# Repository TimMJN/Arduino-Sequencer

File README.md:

# Arduino Sequencer
This projects contains schematics and firmware for a step sequencer compatible with Eurorack and Kosmo modular synthesizers, based on an Arduino Nano. This is a DIY project, suitable for beginners, although a general knowledge of electronics, basic tools and skills are required to build this sequencer. The schematics presented here feature:

- 8 steps, 2 voices
- Clock/reset/flip direction inputs
- Random sequence switch
- Buffered gate outputs per step
- Buffered CV outputs per voice
- Scale/offset controls
- Glide controls

Any builder is encouraged to experiment and make changed to the project to suit their needs. By the use of 74HC595 Serial-In-Parallel-Out shift registers to drive the step signals, this sequencer can be easily extended to 16, 32, 64 or even more steps. Similarly, additional voice can be easily added. I'll keep updating the project and documentation as I go.

A [short demonstration](https://youtu.be/yhleVjD8cbQ) is available in YouTube. View the [schematic](schematic+BOM/arduino_sequencer.pdf) and [bill of materials](https://htmlpreview.github.io/?https://github.com/TimMJN/Arduino-Sequencer/blob/main/schematic%2BBOM/arduino_sequencer_BOM.html) on this repository.

# Frequently Asked Questions
## The build
#### Do you have PCBs / panels available?
A PCB design for Kosmo format is available, along with a panel drill guide. I might have some PCBs available, please get in touch. However, it is also possible to build this design on perfboard/stripboard. I want to encourage any builder to come up with their own panel layout, make whatever feels natural to them. If you document your work, I'll be happy to add it here for future reference.

#### How to I add more steps?
Simply copy the main sequencer section as many times as you like. The connections between the 74HC595s are noted in the schematic. The latch and clock pins simply connect together, the serial out of each register connects to the serial in of the next. In the code, change the value of `N_STEPS` and voila!

#### How to I add more voices?
Copy the row of potentiometers/diodes in the main sequencer section as many times as you like. Don't forget to also copy the asociated output circuitry!

#### Can I leave out the gate buffers?
Yes you can. It would be best practice the keep them, but they could be replaced by just a protection diode (e.g. 1N1418).

#### Can I leave out the offset/scale/glide?
I would advice against using no buffering at all, but you could replace this section with just a unity gain buffer. It's also possible to leave out only the glide components, in which case you can also do without the non-inverting buffer behind it.

#### Can I leave out the input protection?
This I would strongly advice against. It's very easy to fry the Arduino by plugging in the wrong signal. You could simplify to a voltage clamp using two Schottky diodes, but I don't see the point in not doing it properly. If you do go with that option, don't forget to change to input logic to track rising instead of falling edges, as the current set-up inverts the inputs.

#### Can I leave out the randomise switch?
Yes, just simply don't include it.

## The code
#### Why don't you use `shiftOut`?
The serial output code I wrote here does the exact same thing as `shiftOut`. I only adapted it to output any number of steps, as the standard 8 bits by `shiftOut`.

#### What's this `interrupt` business?
This allows that Arduino to stop whatever it's doing when it receives a pulse on the clock input and update to the next step. That means that the polling of the other input pins will never slow down the progressing to the next step. Neat!

## The patch
#### Why can't I change the sequence length?
You can, simply patch the gate of the last step to the reset input.

#### Why can't I set a back-and-forth pattern?
You can, simply patch one or two of the gates to the flip input.

# License
All designs in this repository are released under GPL-3.0 licence. Feel free to use and adapt them to your heart's desire. I only ask to refrain from mass-production and commercialisation of PCBs/modules, as I rely on PCB sales for funding new module designs. If you use (parts of) my designs in your own modules, please credit me on your schematics and PCBs to help users find the original creator. I call upon your good conscience to make fair use of my work shared here.

# Support
If you like the resources I have made available here, and wish to support the development of new modules, feel free to buy me a few components through a small donation. I mainly design modules for fun, but you probably already know it can be a costly endeavour. All small contributions help me, thank you very much!

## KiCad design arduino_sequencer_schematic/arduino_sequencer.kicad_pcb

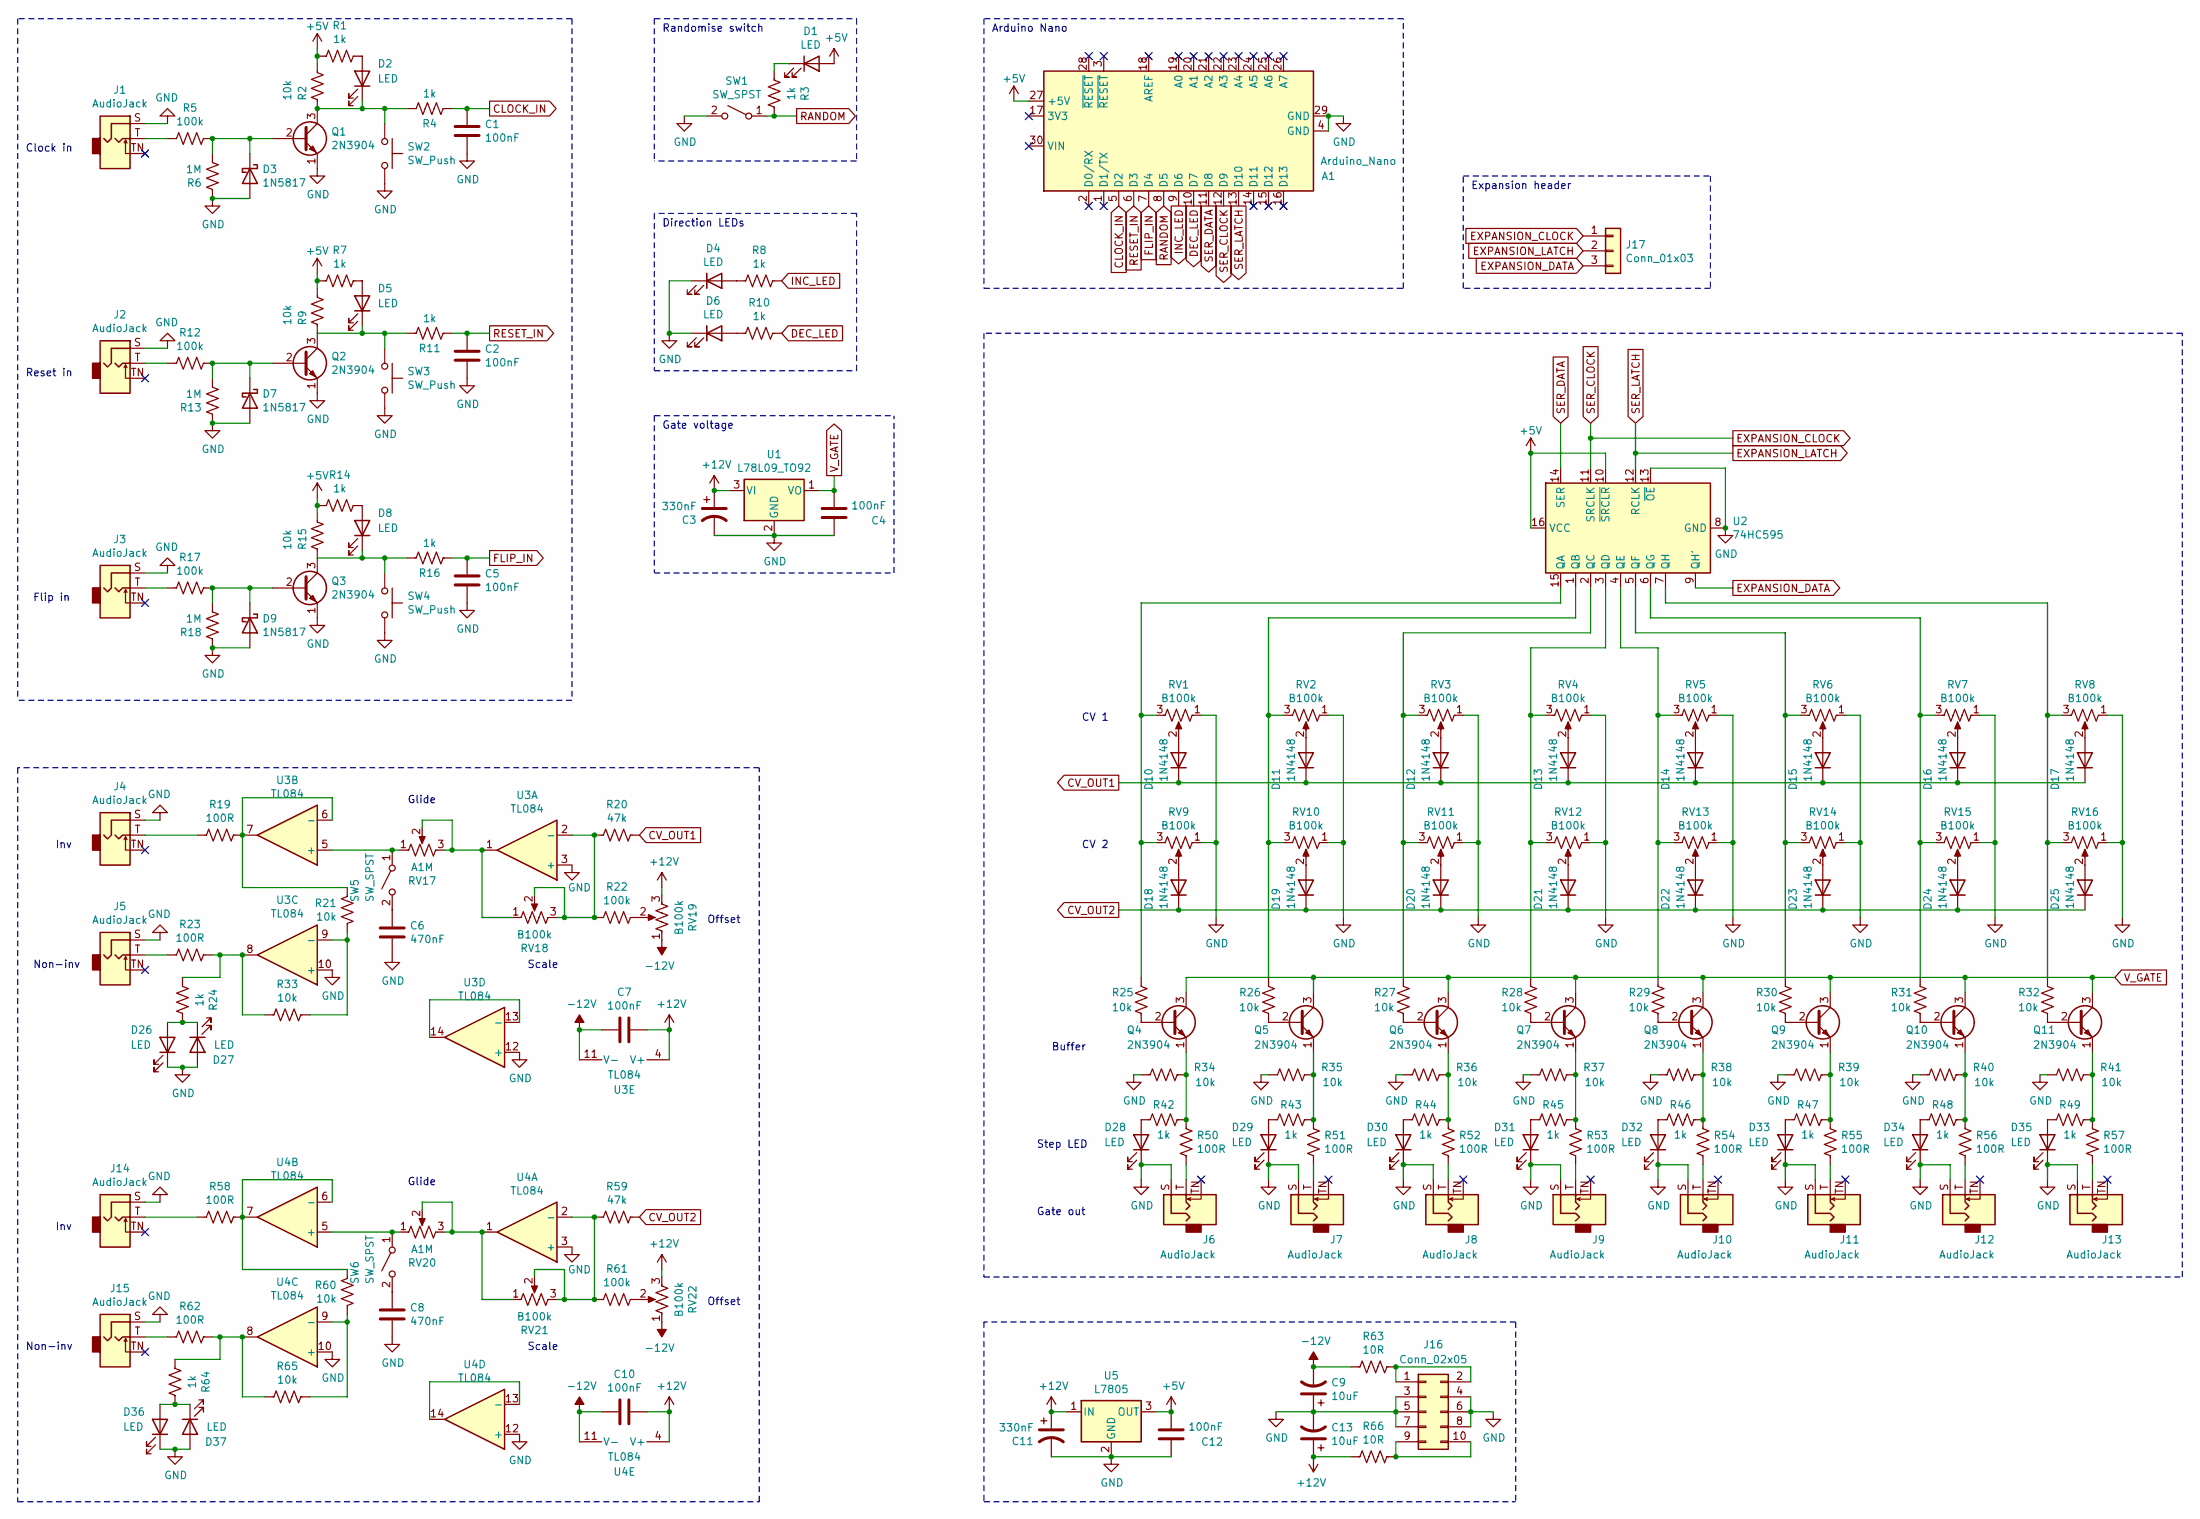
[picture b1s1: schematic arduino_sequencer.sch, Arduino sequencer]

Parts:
A1: Arduino_Nano; Arduino_Nano_2x_header
C1, C2, C4, C5, C7, C10, C12: 100nF; C_Disc_D6.0mm_W2.5mm_P5.00mm
C3, C11: 330nF; CP_Radial_D10.0mm_P3.80mm
C6, C8: 470nF; C_Disc_D14.5mm_W5.0mm_P7.50mm
C9, C13: 10uF; CP_Radial_D10.0mm_P3.80mm
D1, D2, D4, D5, D6, D8, D26, D27, D28, D29, D30, D31, D32, D33, D34, D35, D36, D37: LED; LED_D5.0mm
D3, D7, D9: 1N5817; D_DO-41_SOD81_P10.16mm_Horizontal
D10, D11, D12, D13, D14, D15, D16, D17, D18, D19, D20, D21, D22, D23, D24, D25: 1N4148; D_DO-35_SOD27_P7.62mm_Horizontal
J1, J2, J3, J4, J5, J6, J7, J8, J9, J10, J11, J12, J13, J14, J15: AudioJack; Jack_JST_conn_1x02_P2.50mm
J16: Conn_02x05; IDC-Header_2x05_P2.54mm_Vertical
J17: Conn_01x03; JST_EH_B3B-EH-A_1x03_P2.50mm_Vertical
Q1, Q2, Q3, Q4, Q5, Q6, Q7, Q8, Q9, Q10, Q11: 2N3904; TO-92_Inline
R1, R3, R4, R7, R8, R10, R11, R14, R16, R24, R42, R43, R44, R45, R46, R47, R48, R49, R64: 1k; R_Axial_DIN0207_L6.3mm_D2.5mm_P10.16mm_Horizontal_Value_Sil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
R2, R9, R15, R21, R25, R26, R27, R28, R29, R30, R31, R32, R33, R34, R35, R36, R37, R38, R39, R40, R41, R60, R65: 10k; R_Axial_DIN0207_L6.3mm_D2.5mm_P10.16mm_Horizontal_Value_Sil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
R5, R12, R17, R22, R61: 100k; R_Axial_DIN0207_L6.3mm_D2.5mm_P10.16mm_Horizontal_Value_Sil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
R6, R13, R18: 1M; R_Axial_DIN0207_L6.3mm_D2.5mm_P10.16mm_Horizontal_Value_Sil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
R19, R23, R50, R51, R52, R53, R54, R55, R56, R57, R58, R62: 100R; R_Axial_DIN0207_L6.3mm_D2.5mm_P10.16mm_Horizontal_Value_Sil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
R20, R59: 47k; R_Axial_DIN0207_L6.3mm_D2.5mm_P10.16mm_Horizontal_Value_Sil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
R63, R66: 10R; R_Axial_DIN0207_L6.3mm_D2.5mm_P10.16mm_Horizontal_Value_Sil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
RV1, RV2, RV3, RV4, RV5, RV6, RV7, RV8, RV9, RV10, RV11, RV12, RV13, RV14, RV15, RV16, RV18, RV19, RV21, RV22: B100k; Potentiometer_Alpha_RD901F-40-00D_Single_Vertical
RV17, RV20: A1M; Potentiometer_Alpha_RD901F-40-00D_Single_Vertical
SW1, SW5, SW6: SW_SPST; Switch_SP
SW2, SW3, SW4: SW_Push; Mom_push_button_PBS-110
U1: L78L09_TO92; TO-92_Inline
U2: 74HC595; DIP-16_W7.62mm
U3, U4: TL084; DIP-14_W7.62mm
U5: L7805; TO-220-3_Vertical

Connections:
+5V: A1.27 (+5V), C12.2, D1.2 (A), R1.2, R2.1, R7.2, R9.1, R14.2, R15.1, U2.10 (~SRCLR), U2.16 (VCC), U5.3 (OUT)
+12V: C3.1, C7.1, C10.1, C11.1, C13.1, R66.2, RV19.3, RV22.3, U1.3 (VI), U3.4 (V+), U4.4 (V+), U5.1 (IN)
-12V: C7.2, C9.2, C10.2, R63.2, RV19.1, RV22.1, U3.11 (V-), U4.11 (V-)
CLOCK_IN: A1.5 (D2), C1.1, R4.2
CV_OUT1: D10.1 (K), D11.1 (K), D12.1 (K), D13.1 (K), D14.1 (K), D15.1 (K), D16.1 (K), D17.1 (K), R20.1
CV_OUT2: D18.1 (K), D19.1 (K), D20.1 (K), D21.1 (K), D22.1 (K), D23.1 (K), D24.1 (K), D25.1 (K), R59.1
DEC_LED: A1.10 (D7), R10.1
EXPANSION_CLOCK: A1.12 (D9), J17.1, U2.11 (SRCLK)
EXPANSION_DATA: J17.3, U2.9 (QH')
EXPANSION_LATCH: A1.13 (D10), J17.2, U2.12 (RCLK)
FLIP_IN: A1.7 (D4), C5.1, R16.2
GND: A1.4 (GND), A1.29 (GND), C1.2, C2.2, C3.2, C4.1, C5.2, C6.2, C8.2, C9.1, C11.2, C12.1, C13.2, D3.2 (A), D4.1 (K), D6.1 (K), D7.2 (A), D9.2 (A), D26.1 (K), D27.2 (A), D28.1 (K), D29.1 (K), D30.1 (K), D31.1 (K), D32.1 (K), D33.1 (K), D34.1 (K), D35.1 (K), D36.1 (K), D37.2 (A), J1.S, J2.S, J3.S, J4.S, J5.S, J6.S, J7.S, J8.S, J9.S, J10.S, J11.S, J12.S, J13.S, J14.S, J15.S, J16.3, J16.4, J16.5, J16.6, J16.7, J16.8, Q1.1 (E), Q2.1 (E), Q3.1 (E), R6.1, R13.1, R18.1, R34.1, R35.1, R36.1, R37.1, R38.1, R39.1, R40.1, R41.1, RV1.1, RV2.1, RV3.1, RV4.1, RV5.1, RV6.1, RV7.1, RV8.1, RV9.1, RV10.1, RV11.1, RV12.1, RV13.1, RV14.1, RV15.1, RV16.1, SW1.2 (B), SW2.2, SW3.2, SW4.2, U1.2 (GND), U2.8 (GND), U2.13 (~OE), U3.3 (+), U3.10 (+), U3.12 (+), U4.3 (+), U4.10 (+), U4.12 (+), U5.2 (GND)
INC_LED: A1.9 (D6), R8.1
unnamed: C6.1, SW5.2 (B)
unnamed: C8.1, SW6.2 (B)
unnamed: D1.1 (K), R3.2
unnamed: D2.1 (K), Q1.3 (C), R2.2, R4.1, SW2.1
unnamed: D2.2 (A), R1.1
unnamed: D3.1 (K), Q1.2 (B), R5.1, R6.2
unnamed: D4.2 (A), R8.2
unnamed: D5.1 (K), Q2.3 (C), R9.2, R11.1, SW3.1
unnamed: D5.2 (A), R7.1
unnamed: D6.2 (A), R10.2
unnamed: D7.1 (K), Q2.2 (B), R12.1, R13.2
unnamed: D8.1 (K), Q3.3 (C), R15.2, R16.1, SW4.1
unnamed: D8.2 (A), R14.1
unnamed: D9.1 (K), Q3.2 (B), R17.1, R18.2
unnamed: D10.2 (A), RV1.2
unnamed: D11.2 (A), RV2.2
unnamed: D12.2 (A), RV3.2
unnamed: D13.2 (A), RV4.2
unnamed: D14.2 (A), RV5.2
unnamed: D15.2 (A), RV6.2
unnamed: D16.2 (A), RV7.2
unnamed: D17.2 (A), RV8.2
unnamed: D18.2 (A), RV9.2
unnamed: D19.2 (A), RV10.2
unnamed: D20.2 (A), RV11.2
unnamed: D21.2 (A), RV12.2
unnamed: D22.2 (A), RV13.2
unnamed: D23.2 (A), RV14.2
unnamed: D24.2 (A), RV15.2
unnamed: D25.2 (A), RV16.2
unnamed: D26.2 (A), D27.1 (K), R24.1
unnamed: D28.2 (A), R42.1
unnamed: D29.2 (A), R43.1
unnamed: D30.2 (A), R44.1
unnamed: D31.2 (A), R45.1
unnamed: D32.2 (A), R46.1
unnamed: D33.2 (A), R47.1
unnamed: D34.2 (A), R48.1
unnamed: D35.2 (A), R49.1
unnamed: D36.2 (A), D37.1 (K), R64.1
unnamed: J1.T, R5.2
unnamed: J2.T, R12.2
unnamed: J3.T, R17.2
unnamed: J4.T, R19.2
unnamed: J5.T, R23.2
unnamed: J6.T, R50.2
unnamed: J7.T, R51.2
unnamed: J8.T, R52.2
unnamed: J9.T, R53.2
unnamed: J10.T, R54.2
unnamed: J11.T, R55.2
unnamed: J12.T, R56.2
unnamed: J13.T, R57.2
unnamed: J14.T, R58.2
unnamed: J15.T, R62.2
unnamed: J16.1, J16.2, R63.1
unnamed: J16.9, J16.10, R66.1
unnamed: Q4.1 (E), R34.2, R42.2, R50.1
unnamed: Q4.2 (B), R25.2
unnamed: Q5.1 (E), R35.2, R43.2, R51.1
unnamed: Q5.2 (B), R26.2
unnamed: Q6.1 (E), R36.2, R44.2, R52.1
unnamed: Q6.2 (B), R27.2
unnamed: Q7.1 (E), R37.2, R45.2, R53.1
unnamed: Q7.2 (B), R28.2
unnamed: Q8.1 (E), R38.2, R46.2, R54.1
unnamed: Q8.2 (B), R29.2
unnamed: Q9.1 (E), R39.2, R47.2, R55.1
unnamed: Q9.2 (B), R30.2
unnamed: Q10.1 (E), R40.2, R48.2, R56.1
unnamed: Q10.2 (B), R31.2
unnamed: Q11.1 (E), R41.2, R49.2, R57.1
unnamed: Q11.2 (B), R32.2
unnamed: R19.1, R21.2, U3.6 (-), U3.7
unnamed: R20.2, R22.2, RV18.2, RV18.3, U3.2 (-)
unnamed: R21.1, R33.1, U3.9 (-)
unnamed: R22.1, RV19.2
unnamed: R23.1, R24.2, R33.2, U3.8
unnamed: R25.1, RV1.3, RV9.3, U2.15 (QA)
unnamed: R26.1, RV2.3, RV10.3, U2.1 (QB)
unnamed: R27.1, RV3.3, RV11.3, U2.2 (QC)
unnamed: R28.1, RV4.3, RV12.3, U2.3 (QD)
unnamed: R29.1, RV5.3, RV13.3, U2.4 (QE)
unnamed: R30.1, RV6.3, RV14.3, U2.5 (QF)
unnamed: R31.1, RV7.3, RV15.3, U2.6 (QG)
unnamed: R32.1, RV8.3, RV16.3, U2.7 (QH)
unnamed: R58.1, R60.2, U4.6 (-), U4.7
unnamed: R59.2, R61.2, RV21.2, RV21.3, U4.2 (-)
unnamed: R60.1, R65.1, U4.9 (-)
unnamed: R61.1, RV22.2
unnamed: R62.1, R64.2, R65.2, U4.8
unnamed: RV17.1, SW5.1 (A), U3.5 (+)
unnamed: RV17.2, RV17.3, RV18.1, U3.1
unnamed: RV20.1, SW6.1 (A), U4.5 (+)
unnamed: RV20.2, RV20.3, RV21.1, U4.1
unnamed: U3.13 (-), U3.14
unnamed: U4.13 (-), U4.14
RANDOM: A1.8 (D5), R3.1, SW1.1 (A)
RESET_IN: A1.6 (D3), C2.1, R11.2
SER_DATA: A1.11 (D8), U2.14 (SER)
V_GATE: C4.2, Q4.3 (C), Q5.3 (C), Q6.3 (C), Q7.3 (C), Q8.3 (C), Q9.3 (C), Q10.3 (C), Q11.3 (C), U1.1 (VO)

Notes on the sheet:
Offset
Scale
Glide
Inv
Non-inv
Gate out
Direction LEDs
Randomise switch
Clock in
Reset in
Flip in
Arduino Nano
Step LED
Buffer
CV 1
CV 2
Gate voltage
Expansion header

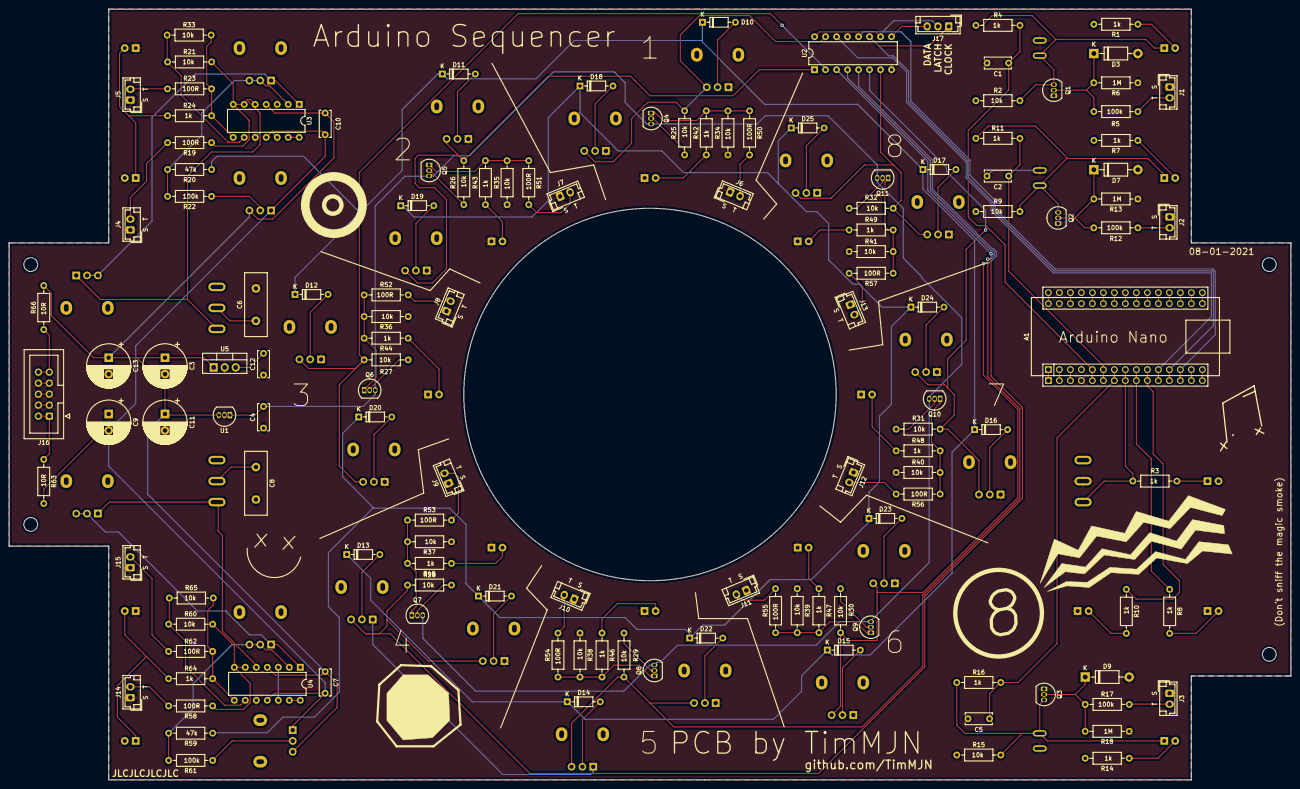
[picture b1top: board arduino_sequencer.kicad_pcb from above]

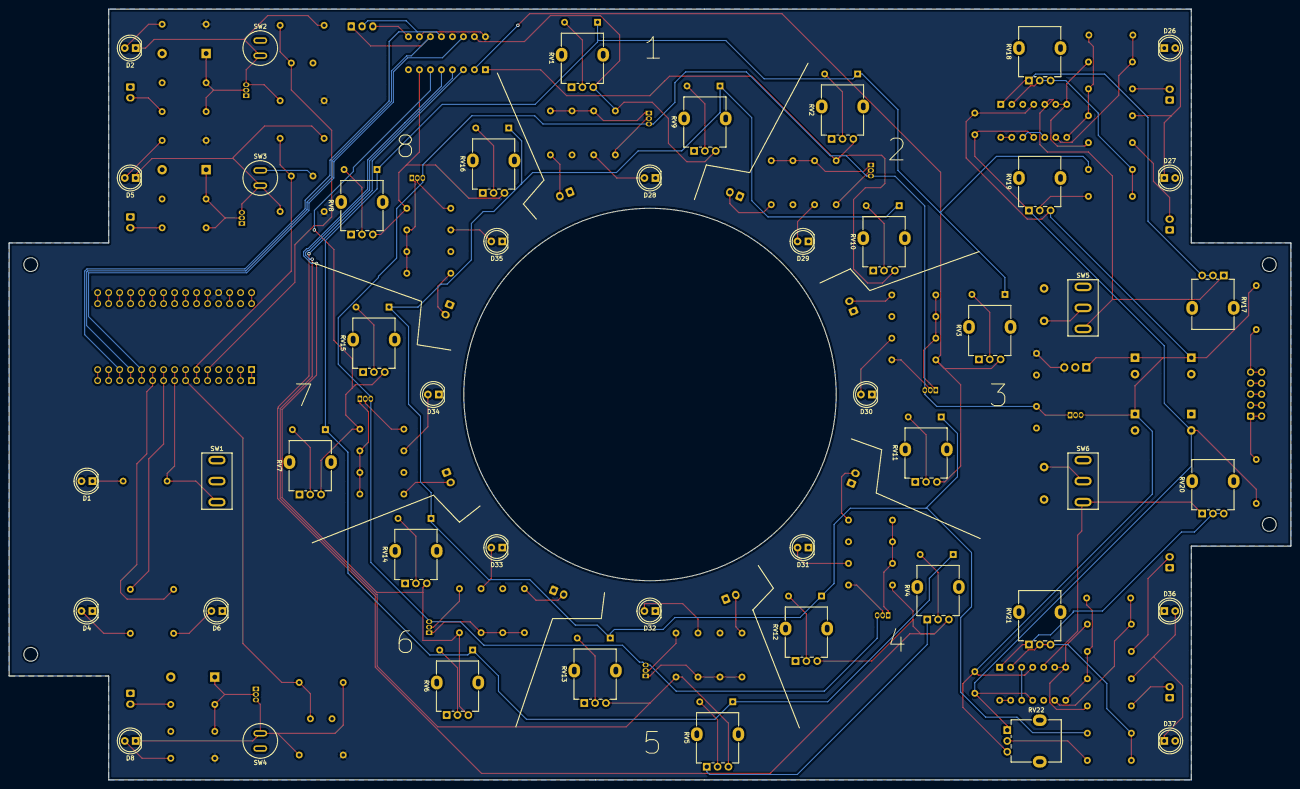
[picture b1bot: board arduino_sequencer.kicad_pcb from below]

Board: 2 copper layers, 296.0 x 178.0 mm, 178 parts (46 on the bottom side), 114 nets.

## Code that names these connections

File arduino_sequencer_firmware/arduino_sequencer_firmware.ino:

////////////////////////////////////////////////////////////////////////////////////////////////////

/* 
 * Arduino Sequencer
 * synthesizer module firmware
 * 
 * by TimMJN
 * 
 * v1.0 
 * 16-01-2021
 * 
 * For schematics and other information, see
 * https://github.com/TimMJN/Arduino-Sequencer
 */

////////////////////////////////////////////////////////////////////////////////////////////////////

// pin definitions
#define CLOCK_PIN     2
#define RESET_PIN     3
#define FLIP_PIN      4
#define RAND_PIN      5
#define INC_LED_PIN   6
#define DEC_LED_PIN   7
#define SER_DATA_PIN  8
#define SER_CLOCK_PIN 9
#define SER_LATCH_PIN 10

#define N_STEPS 8 // number of steps

byte cur_step  = 0; // current step
byte next_step = 0; // next step
bool dir_inc   = true;  // direction (increasing = true, decreasing = false)
bool reset     = false; // has the reset been triggered this step?
bool randomise = false; // turn on/off random sequence

// current and previous states of reset and flip pins
bool cur_reset_state  = true;
bool prev_reset_state = true;
bool cur_flip_state   = true;
bool prev_flip_state  = true;
bool cur_rand_state   = true;
bool prev_rand_state  = true;

////////////////////////////////////////////////////////////////////////////////////////////////////

void setup() {
  // pin modes
  // alternatively ommit external pull up resistors and use INPUT_PULLUP
  pinMode(CLOCK_PIN,     INPUT);
  pinMode(RESET_PIN,     INPUT);
  pinMode(FLIP_PIN,      INPUT);
  pinMode(RAND_PIN,      INPUT_PULLUP);
  pinMode(INC_LED_PIN,   OUTPUT);
  pinMode(DEC_LED_PIN,   OUTPUT);
  pinMode(SER_DATA_PIN,  OUTPUT);
  pinMode(SER_CLOCK_PIN, OUTPUT);
  pinMode(SER_LATCH_PIN, OUTPUT);

  // set up interrupt on clock pin
  attachInterrupt(digitalPinToInterrupt(CLOCK_PIN), take_step, FALLING);
  interrupts();

  // set up randomisation
  randomise       = digitalRead(RAND_PIN) == LOW;
  prev_rand_state = digitalRead(RAND_PIN) == HIGH;

  // set next step and direction LEDs;
  set_next_step();
  set_direction_leds();

  // set output to first step
  set_shift_register(cur_step);
  digitalWrite(SER_LATCH_PIN, HIGH);

  // set shift register to next step
  set_shift_register(next_step);

  // do a small delay to prevent startup affecting inputs
  delay(100);
}

////////////////////////////////////////////////////////////////////////////////////////////////////

void loop() {
  // read reset and flip inputs
  cur_reset_state = digitalRead(RESET_PIN) == HIGH;
  cur_flip_state  = digitalRead(FLIP_PIN ) == HIGH;
  cur_rand_state  = digitalRead(RAND_PIN ) == HIGH;

  // edge detection on reset, flip and randomise inputs
  if (prev_reset_state && (!cur_reset_state)) {
    reset = true;
    set_next_step();
    set_shift_register(next_step); // update shift register
  }

  if (prev_flip_state && (!cur_flip_state)) {
    dir_inc = !dir_inc; // flip direction

    // update next step, shift register and LEDs
    set_next_step();
    set_shift_register(next_step); // update shift register
    set_direction_leds();
  }

  if (prev_rand_state && (!cur_rand_state)) { // turn on randomisation
    randomise = true;
    set_next_step();
    set_shift_register(next_step); // update shift register
  }
  if ((!prev_rand_state) && cur_rand_state) { // turn off randomisation
    randomise = false;
    set_next_step();
    set_shift_register(next_step); // update shift register
  }

  // update previous cycle values
  prev_reset_state = cur_reset_state;
  prev_flip_state  = cur_flip_state;
  prev_rand_state  = cur_rand_state;
}

////////////////////////////////////////////////////////////////////////////////////////////////////

// set what will be the next step
void set_next_step() {
  if (reset) {
    next_step = 0; // go back to step 0
  }
  else if (randomise) {
    next_step = random(0, N_STEPS); // pick a random step
  }
  else {
    if (dir_inc)
      next_step = (cur_step + 1) % N_STEPS; // increase 1 step
    else
      next_step = (cur_step - 1 + N_STEPS) % N_STEPS; // decrease 1 step
  }
}

////////////////////////////////////////////////////////////////////////////////////////////////////

// set the direction LEDs
void set_direction_leds() {
  if (dir_inc) {
    digitalWrite(INC_LED_PIN, HIGH);
    digitalWrite(DEC_LED_PIN, LOW);
  }
  else {
    digitalWrite(DEC_LED_PIN, HIGH);
    digitalWrite(INC_LED_PIN, LOW);
  }
}

////////////////////////////////////////////////////////////////////////////////////////////////////

// write the required state to the shift register
void set_shift_register(byte step_index) {
  noInterrupts(); // do not interrupt writing to the shift register

  // loop over the steps, starting from the last
  for (int i = (N_STEPS - 1); i >= 0; i--) {
    if (i == step_index)
      digitalWrite(SER_DATA_PIN, HIGH); // set current step high
    else
      digitalWrite(SER_DATA_PIN, LOW); // set other steps low
  
    digitalWrite(SER_CLOCK_PIN, HIGH); // give clock pin a pulse
    digitalWrite(SER_CLOCK_PIN, LOW);
  }

  interrupts(); // re-enable interrupts
}

////////////////////////////////////////////////////////////////////////////////////////////////////}

// interrupt function
// push shift register to output, prepare for the next step
void take_step() {
  // push to output register (pulse latch pin)
  digitalWrite(SER_LATCH_PIN, HIGH);
  digitalWrite(SER_LATCH_PIN, LOW);

  // update steps
  cur_step = next_step;
  reset = false;
  set_next_step();

  // update next step to shift register
  set_shift_register(next_step);
}

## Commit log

2020-12-08 Added schematics and firmware
2020-12-08 Create .gitignore
    added gitignore
2020-12-09 Chaged scale pot values to 50k
2020-12-10 Fixed errors in CV interver and gate buffers
2020-12-12 Changed negative input protection diodes to Schottky diodes
2020-12-16 Fixed gate output resistors
2020-12-16 uploaded lib file
2020-12-18 Added additional LEDs
2020-12-18 Added footprints
2020-12-18 update PDF
2020-12-19 started PCB layout
2020-12-19 Changed gate voltage to 9V by default
2020-12-19 PCB update
2020-12-28 Update arduino_sequencer.kicad_pcb
    PCB updates
2020-12-30 added missing GND label
2020-12-30 Added expansion header
2020-12-30 PCB routed
2021-01-03 Footprint updates
2021-01-03 Added resistor values on silkscreen
2021-01-03 fixed arduino reset/flip pin inconsistency
2021-01-03 added delay during startup
2021-01-03 Move filter resistor
    For improved stability (no faulty triggers)
2021-01-03 moved lowering of latch pin to interrupt
2021-01-07 Finetuned gain/offset ranges
2021-01-07 Date update
2021-01-07 Fixed potentiometer directions
2021-01-08 prepare for production
2021-01-08 added BOM
2021-01-08 added panel drill guide
2021-01-08 Pull all KiCad files
    I've decided to remove all KiCad files from the repository, in order to keep the design a bit more in my own hands. I will continue publishing schematics and layouts as PDFs, so anyone can reproduce 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
2021-01-09 Added PCB layout files
2021-01-16 formatting
2021-01-16 added URL
2021-01-19 PCB updates
2021-03-05 Added build photos
2021-03-05 increased value of debouncing caps
2021-03-05 removed 9V supply
2021-03-07 increase output impedance to 1k
2021-03-07 Decouple gain/offset
2021-03-09 schematic cleanup
2021-04-11 bug fix
2021-04-24 Added decoupling cap to Arduino
2021-04-24 BOM update
2021-05-21 Scale pot value fix
2021-06-08 moved pcb files
2021-06-26 added renders
2021-07-24 typo fix
2021-08-19 added interactive BOM
2021-11-15 update decoupling caps
2021-11-28 added dimensions to drill guide
2022-05-29 update PCB files
2022-05-29 remove old PCB files
2022-05-29 added datasheets
2022-06-27 schematic update
    switch from diodes to resistors for adding cvs, replace B200k pot with B10k
2024-05-26 rename dirs
